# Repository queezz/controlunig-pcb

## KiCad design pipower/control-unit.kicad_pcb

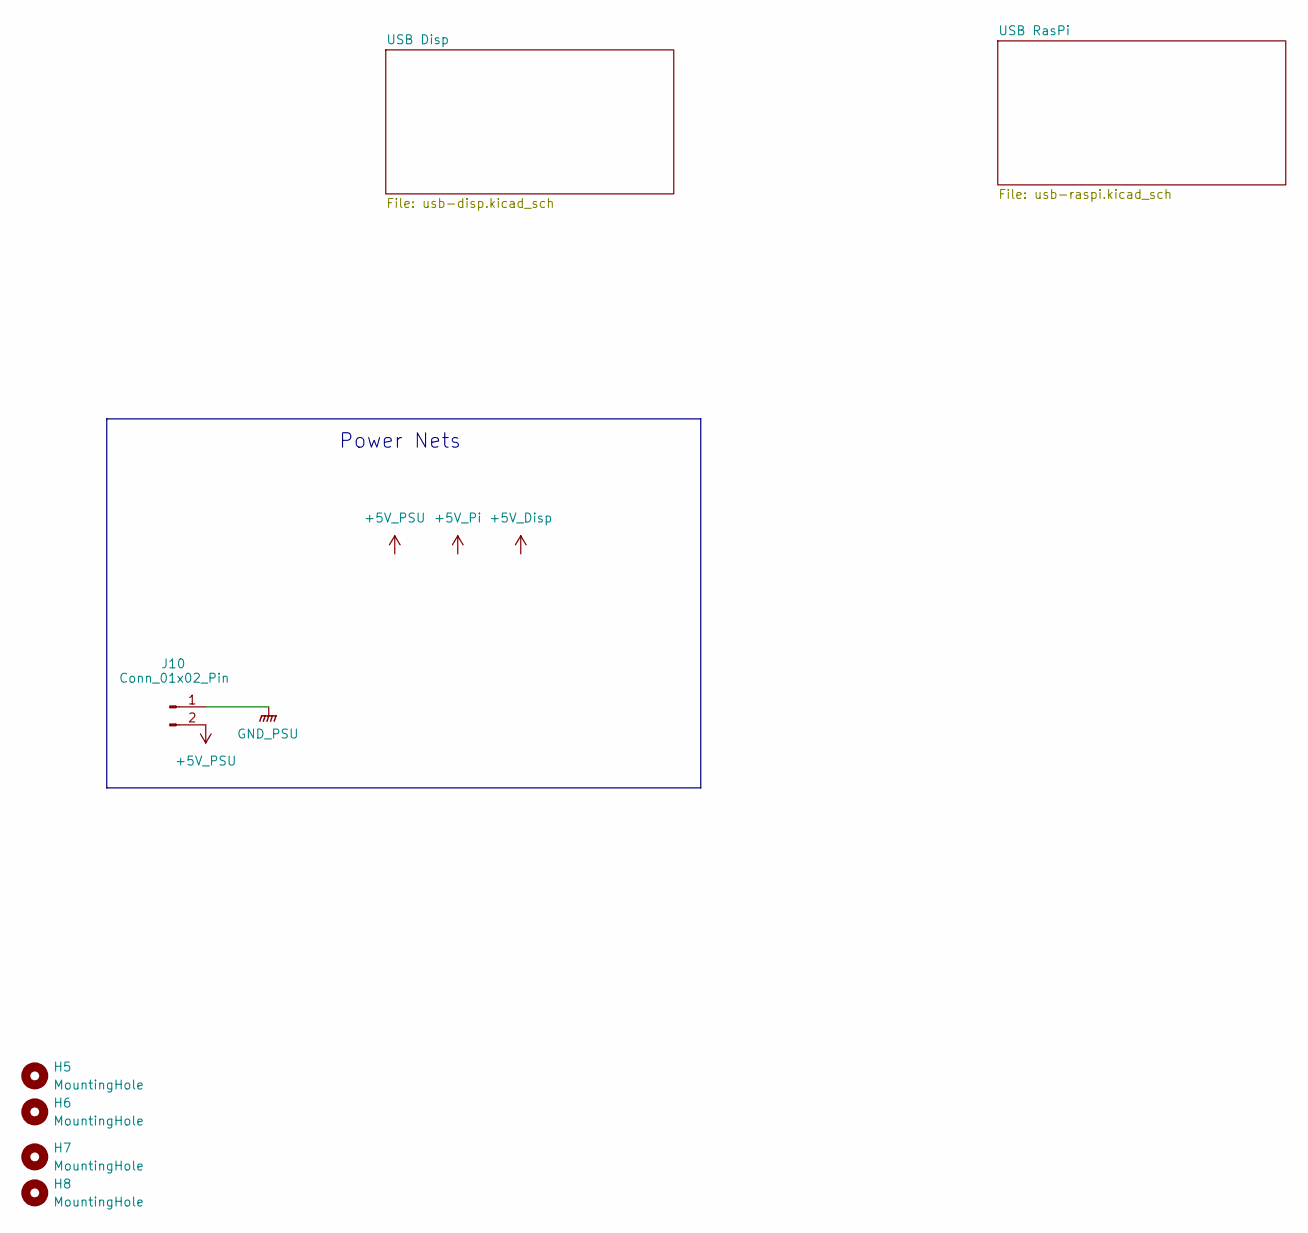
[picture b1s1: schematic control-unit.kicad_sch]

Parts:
H5, H6, H7, H8: MountingHole; MountingHole_3.2mm
J10: Conn_01x02_Pin; JST_VH_B2P-VH-B_1x02_P3.96mm_Vertical

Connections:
+5V_PSU: J10.2; also elsewhere on the board
GND_PSU: J10.1; also elsewhere on the board

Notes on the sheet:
Power Nets

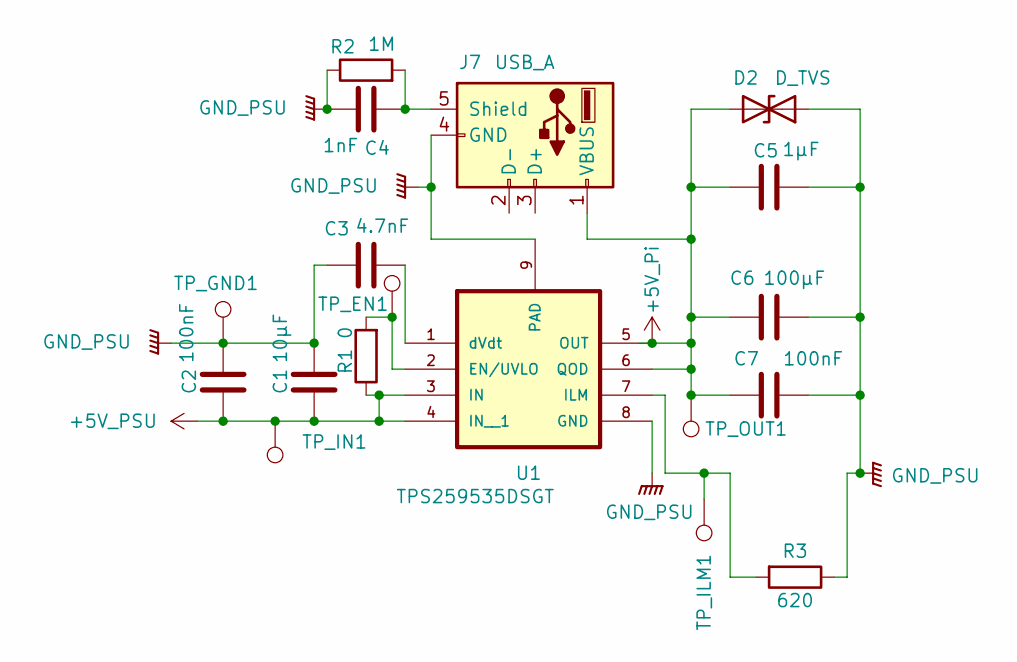
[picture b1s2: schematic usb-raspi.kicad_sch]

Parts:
C1: 10µF; C_0805_2012Metric
C2, C7: 100nF; C_0805_2012Metric
C3: 4.7nF; C_0805_2012Metric
C4: 1nF; C_0805_2012Metric
C5: 1µF; C_0805_2012Metric
C6: 100µF; CP_Elec_6.3x5.8
D2: D_TVS; D_SOD-323_HandSoldering
J7: USB_A; USB_A_Molex_67643_Horizontal
R1: 0; R_0603_1608Metric
R2: 1M; R_0805_2012Metric
R3: 620; R_0805_2012Metric
TP_EN1: TestPoint; TestPoint_Pad_1.0x1.0mm
TP_GND1: TestPoint; TestPoint_Pad_1.0x1.0mm
TP_ILM1: TestPoint; TestPoint_Pad_1.0x1.0mm
TP_IN1: TestPoint; TestPoint_Pad_1.0x1.0mm
TP_OUT1: TestPoint; TestPoint_Pad_1.0x1.0mm
U1: TPS259535DSGT; WSON-8-1EP_2x2mm_P0.5mm_EP0.9x1.6mm

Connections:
+5V_PSU: C1.2, C2.2, R1.1, TP_IN1.1, U1.3 (IN), U1.4 (IN__1); also elsewhere on the board
+5V_Pi: C5.1, C6.1, C7.2, D2.2 (A2), J7.1 (VBUS), TP_OUT1.1, U1.5 (OUT), U1.6 (QOD)
GND_PSU: C1.1, C2.1, C3.1, C4.2, C5.2, C6.2, C7.1, D2.1 (A1), J7.4 (GND), R2.1, R3.1, TP_GND1.1, U1.8 (GND), U1.9 (PAD); also elsewhere on the board
unnamed: C4.1, J7.5 (Shield), R2.2
unnamed: R1.2, TP_EN1.1, U1.2 (EN/UVLO)
unnamed: R3.2, TP_ILM1.1, U1.7 (ILM)
unnamed: C3.2, U1.1 (dVdt)

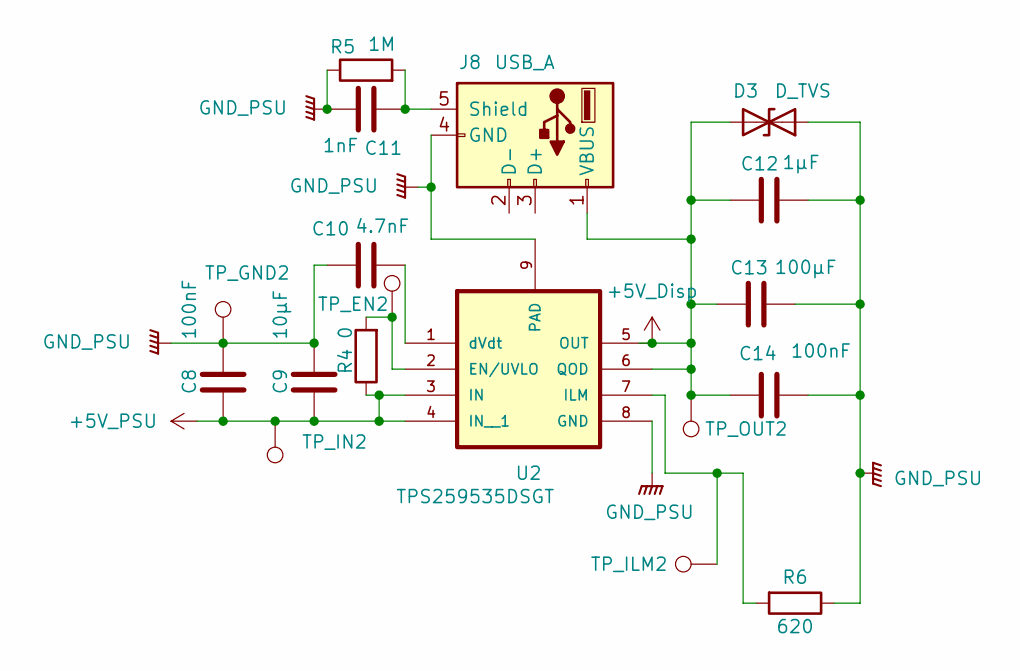
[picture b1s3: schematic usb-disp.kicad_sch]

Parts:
C8, C14: 100nF; C_0805_2012Metric
C9: 10µF; C_0805_2012Metric
C10: 4.7nF; C_0805_2012Metric
C11: 1nF; C_0805_2012Metric
C12: 1µF; C_0805_2012Metric
C13: 100µF; CP_Elec_6.3x5.8
D3: D_TVS; D_SOD-323_HandSoldering
J8: USB_A; USB_A_Molex_67643_Horizontal
R4: 0; R_0603_1608Metric
R5: 1M; R_0805_2012Metric
R6: 620; R_0805_2012Metric
TP_EN2: TestPoint; TestPoint_Pad_1.0x1.0mm
TP_GND2: TestPoint; TestPoint_Pad_1.0x1.0mm
TP_ILM2: TestPoint; TestPoint_Pad_1.0x1.0mm
TP_IN2: TestPoint; TestPoint_Pad_1.0x1.0mm
TP_OUT2: TestPoint; TestPoint_Pad_1.0x1.0mm
U2: TPS259535DSGT; WSON-8-1EP_2x2mm_P0.5mm_EP0.9x1.6mm

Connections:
+5V_Disp: C12.1, C13.1, C14.2, D3.2 (A2), J8.1 (VBUS), TP_OUT2.1, U2.5 (OUT), U2.6 (QOD)
+5V_PSU: C8.2, C9.2, R4.1, TP_IN2.1, U2.3 (IN), U2.4 (IN__1); also elsewhere on the board
GND_PSU: C8.1, C9.1, C10.1, C11.2, C12.2, C13.2, C14.1, D3.1 (A1), J8.4 (GND), R5.1, R6.1, TP_GND2.1, U2.8 (GND), U2.9 (PAD); also elsewhere on the board
unnamed: C11.1, J8.5 (Shield), R5.2
unnamed: R4.2, TP_EN2.1, U2.2 (EN/UVLO)
unnamed: R6.2, TP_ILM2.1, U2.7 (ILM)
unnamed: C10.2, U2.1 (dVdt)

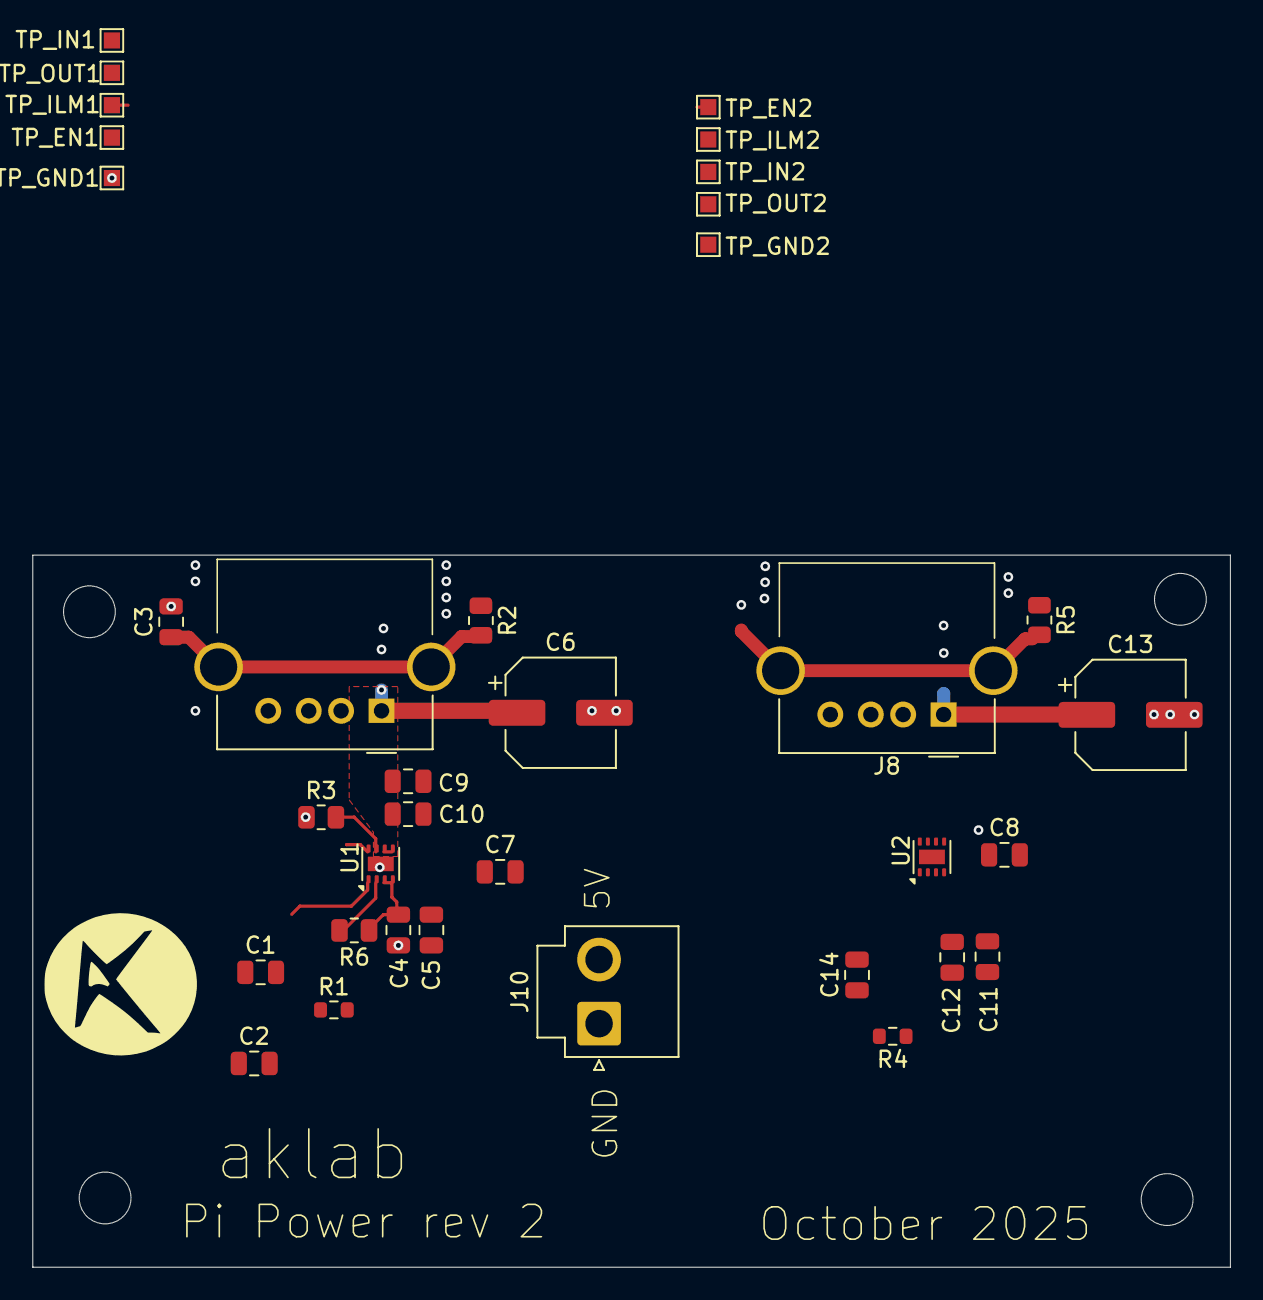
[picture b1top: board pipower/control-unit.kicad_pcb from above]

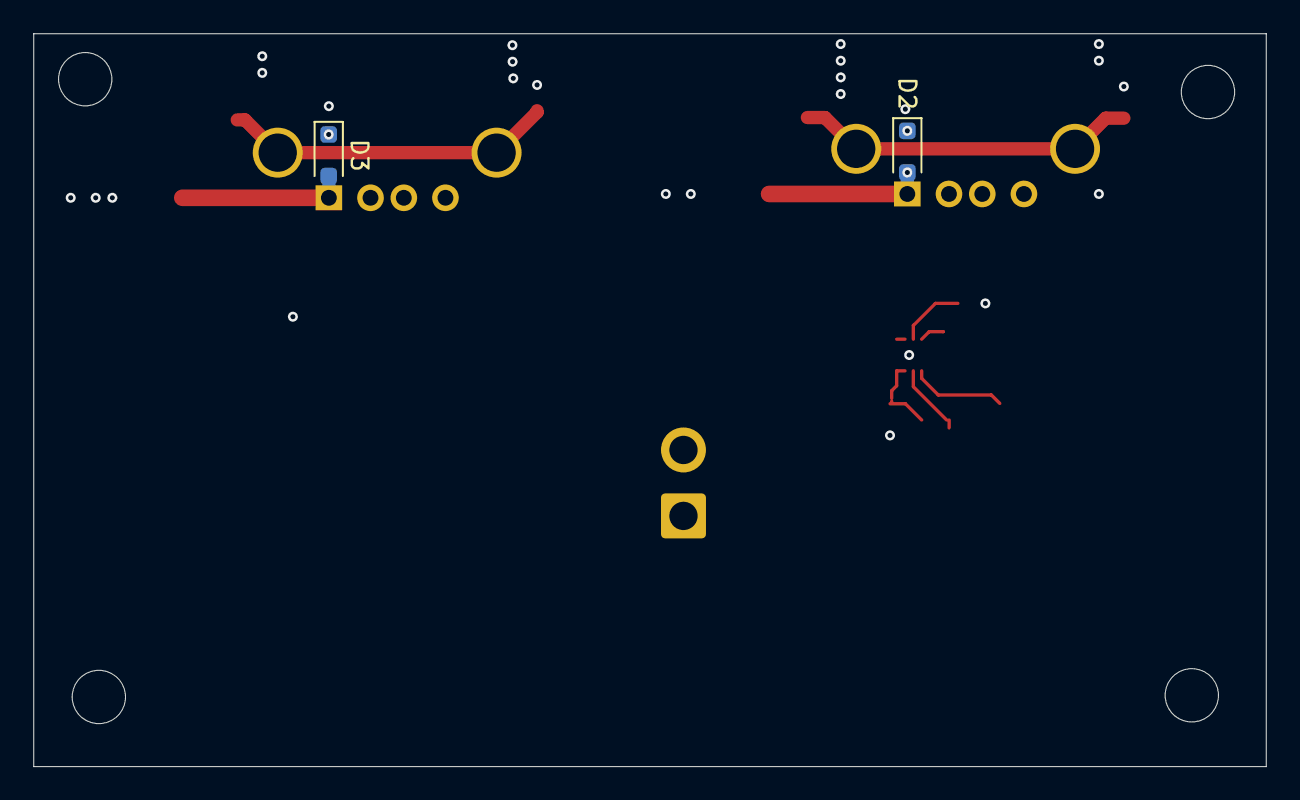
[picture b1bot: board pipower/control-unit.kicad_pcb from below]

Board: 2 copper layers, 74.0 x 44.0 mm, 41 parts (2 on the bottom side), 12 nets.

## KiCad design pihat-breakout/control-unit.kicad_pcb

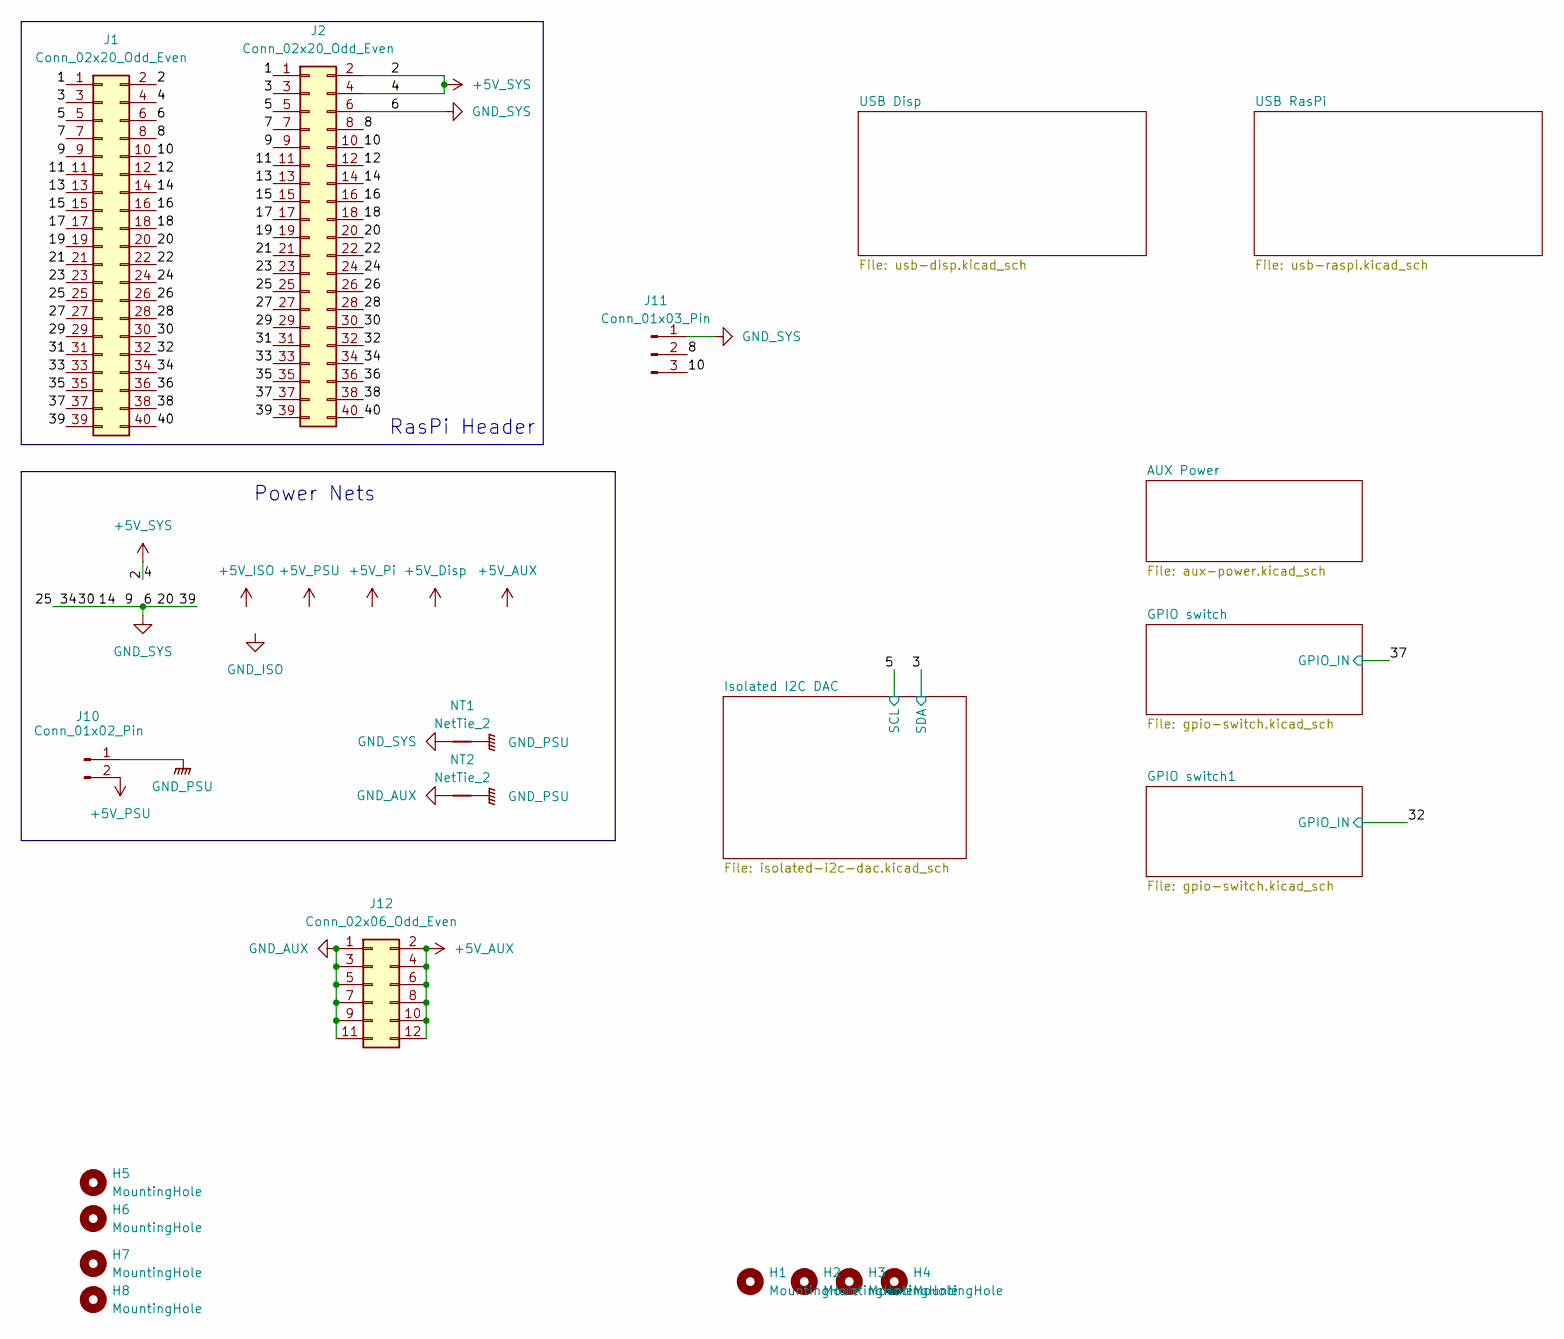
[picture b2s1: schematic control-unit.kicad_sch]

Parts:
H1, H2, H3, H4: MountingHole; MountingHole_2.7mm
H5, H6, H7, H8: MountingHole; MountingHole_3.2mm
J1, J2: Conn_02x20_Odd_Even; RasPiHeader_2x20_P2.54mm_Vertical
J10: Conn_01x02_Pin; JST_VH_B2P-VH-B_1x02_P3.96mm_Vertical
J11: Conn_01x03_Pin; JST_XH_B3B-XH-A_1x03_P2.50mm_Vertical
J12: Conn_02x06_Odd_Even; PinHeader_2x06_P2.54mm_Vertical
NT1, NT2: NetTie_2; NetTie-2_SMD_Pad2.0mm

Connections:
+5V_AUX: J12.2, J12.4, J12.6, J12.8, J12.10, J12.12; also elsewhere on the board
+5V_PSU: J10.2; also elsewhere on the board
+5V_SYS: J1.2, J1.4, J2.2, J2.4; also elsewhere on the board
/1: J1.1, J2.1
/3: J1.3, J2.3; also elsewhere on the board
/5: J1.5, J2.5; also elsewhere on the board
/7: J1.7, J2.7
/8: J1.8, J2.8, J11.2
/10: J1.10, J2.10, J11.3
/11: J1.11, J2.11
/12: J1.12, J2.12
/13: J1.13, J2.13
/15: J1.15, J2.15
/16: J1.16, J2.16
/17: J1.17, J2.17
/18: J1.18, J2.18
/19: J1.19, J2.19
/21: J1.21, J2.21
/22: J1.22, J2.22
/23: J1.23, J2.23
/24: J1.24, J2.24
/26: J1.26, J2.26
/27: J1.27, J2.27
/28: J1.28, J2.28
/29: J1.29, J2.29
/31: J1.31, J2.31
/32: J1.32, J2.32; also elsewhere on the board
/33: J1.33, J2.33
/35: J1.35, J2.35
/36: J1.36, J2.36
/37: J1.37, J2.37; also elsewhere on the board
/38: J1.38, J2.38
/40: J1.40, J2.40
GND_AUX: J12.1, J12.3, J12.5, J12.7, J12.9, J12.11, NT2.1; also elsewhere on the board
GND_PSU: J10.1, NT1.2, NT2.2; also elsewhere on the board
GND_SYS: J1.6, J1.9, J1.14, J1.20, J1.25, J1.30, J1.34, J1.39, J2.6, J2.9, J2.14, J2.20, J2.25, J2.30, J2.34, J2.39, J11.1, NT1.1; also elsewhere on the board

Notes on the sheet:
RasPi Header
Power Nets

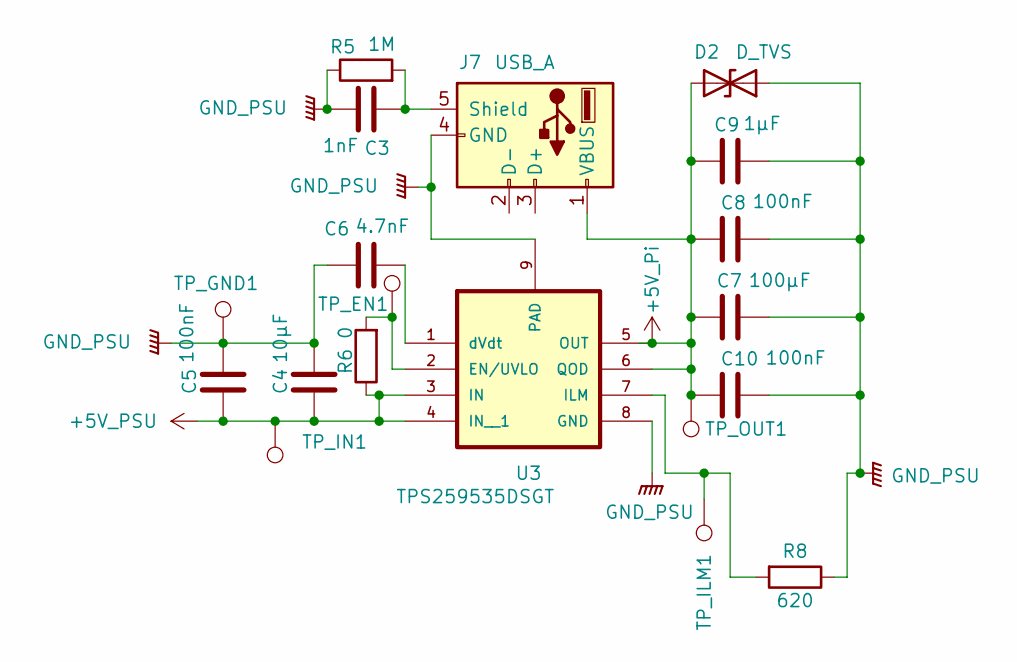
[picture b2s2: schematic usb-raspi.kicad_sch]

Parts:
C3: 1nF; C_0603_1608Metric
C4: 10µF; C_0603_1608Metric
C5, C8, C10: 100nF; C_0603_1608Metric
C6: 4.7nF; C_0603_1608Metric
C7: 100µF; CP_Elec_6.3x5.8
C9: 1µF; C_0603_1608Metric
D2: D_TVS; D_SOD-323_HandSoldering
J7: USB_A; USB_A_Molex_67643_Horizontal
R5: 1M; R_0603_1608Metric
R6: 0; R_0603_1608Metric
R8: 620; R_0603_1608Metric
TP_EN1: TestPoint; TestPoint_Pad_1.0x1.0mm
TP_GND1: TestPoint; TestPoint_Pad_1.0x1.0mm
TP_ILM1: TestPoint; TestPoint_Pad_1.0x1.0mm
TP_IN1: TestPoint; TestPoint_Pad_1.0x1.0mm
TP_OUT1: TestPoint; TestPoint_Pad_1.0x1.0mm
U3: TPS259535DSGT; WSON-8-1EP_3x3mm_P0.5mm_EP1.6x2.0mm

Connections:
+5V_PSU: C4.2, C5.2, R6.1, TP_IN1.1, U3.3 (IN), U3.4 (IN__1); also elsewhere on the board
+5V_Pi: C7.1, C8.2, C9.1, C10.2, D2.2 (A2), J7.1 (VBUS), TP_OUT1.1, U3.5 (OUT), U3.6 (QOD)
GND_PSU: C3.2, C4.1, C5.1, C6.1, C7.2, C8.1, C9.2, C10.1, D2.1 (A1), J7.4 (GND), R5.1, R8.1, TP_GND1.1, U3.8 (GND), U3.9 (PAD); also elsewhere on the board
unnamed: C3.1, J7.5 (Shield), R5.2
unnamed: R6.2, TP_EN1.1, U3.2 (EN/UVLO)
unnamed: R8.2, TP_ILM1.1, U3.7 (ILM)
unnamed: C6.2, U3.1 (dVdt)

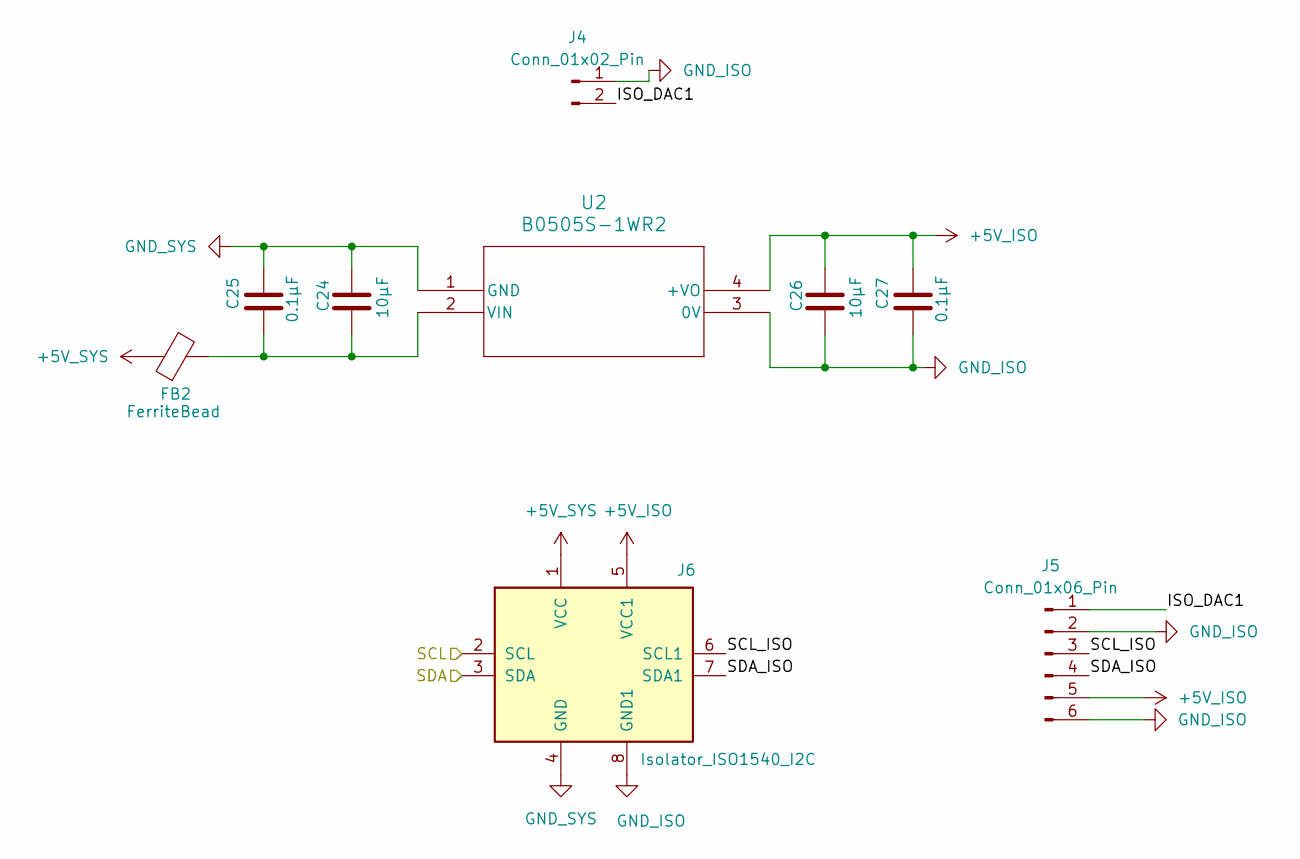
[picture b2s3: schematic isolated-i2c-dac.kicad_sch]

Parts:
C24: 10µF; C_0805_2012Metric
C25, C27: 0.1µF; C_0603_1608Metric
C26: 10µF; C_1206_3216Metric
FB2: FerriteBead; R_0805_2012Metric
J4: Conn_01x02_Pin; JST_XH_B2B-XH-A_1x02_P2.50mm_Vertical
J5: Conn_01x06_Pin; MCP4725_module
J6: Isolator_ISO1540_I2C; Isolator_ISO_1540_module
U2: B0505S-1WR2; B0505S-1WR2_MNS

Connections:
+5V_ISO: C26.1, C27.1, J5.5, J6.5 (VCC1), U2.4 (+VO)
+5V_SYS: FB2.1, J6.1 (VCC); also elsewhere on the board
/3: J6.3 (SDA); also elsewhere on the board
/5: J6.2 (SCL); also elsewhere on the board
/Isolated I2C DAC/ISO_DAC1: J4.2, J5.1
/Isolated I2C DAC/SCL_ISO: J5.3, J6.6 (SCL1)
/Isolated I2C DAC/SDA_ISO: J5.4, J6.7 (SDA1)
GND_ISO: C26.2, C27.2, J4.1, J5.2, J5.6, J6.8 (GND1), U2.3 (0V)
GND_SYS: C24.1, C25.1, J6.4 (GND), U2.1 (GND); also elsewhere on the board
unnamed: C24.2, C25.2, FB2.2, U2.2 (VIN)

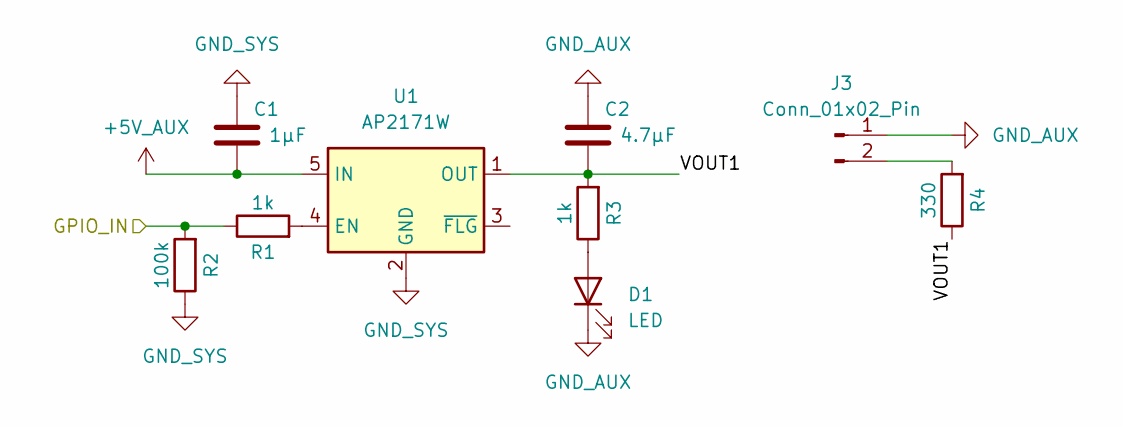
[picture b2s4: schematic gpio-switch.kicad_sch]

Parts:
C1: 1µF; C_0603_1608Metric
C2: 4.7µF; C_0603_1608Metric
D1: LED; LED_0603_1608Metric
J3: Conn_01x02_Pin; JST_XH_B2B-XH-A_1x02_P2.50mm_Vertical
R1, R3: 1k; R_0603_1608Metric
R2: 100k; R_0603_1608Metric
R4: 330; R_0603_1608Metric
U1: AP2171W; SOT-23-5

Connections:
+5V_AUX: C1.2, U1.5 (IN); also elsewhere on the board
/37: R1.1, R2.2; also elsewhere on the board
/GPIO switch/VOUT1: C2.2, R3.2, R4.1, U1.1 (OUT)
GND_AUX: C2.1, D1.1 (K), J3.1; also elsewhere on the board
GND_SYS: C1.1, R2.1, U1.2 (GND); also elsewhere on the board
unnamed: D1.2 (A), R3.1
unnamed: J3.2, R4.2
unnamed: R1.2, U1.4 (EN)

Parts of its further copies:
C22: 1µF; C_0603_1608Metric
C23: 4.7µF; C_0603_1608Metric
D6: LED; LED_0603_1608Metric
J9: Conn_01x02_Pin; JST_XH_B2B-XH-A_1x02_P2.50mm_Vertical
R12: 100k; R_0603_1608Metric
R14, R15: 1k; R_0603_1608Metric
R16: 330; R_0603_1608Metric
U6: AP2171W; SOT-23-5

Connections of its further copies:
+5V_AUX: C22.2, U6.5 (IN); also elsewhere on the board
/32: R12.2, R14.1; also elsewhere on the board
/GPIO switch1/VOUT1: C23.2, R15.2, R16.1, U6.1 (OUT)
GND_AUX: C23.1, D6.1 (K), J9.1; also elsewhere on the board
GND_SYS: C22.1, R12.1, U6.2 (GND); also elsewhere on the board
unnamed: D6.2 (A), R15.1
unnamed: J9.2, R16.2
unnamed: R14.2, U6.4 (EN)

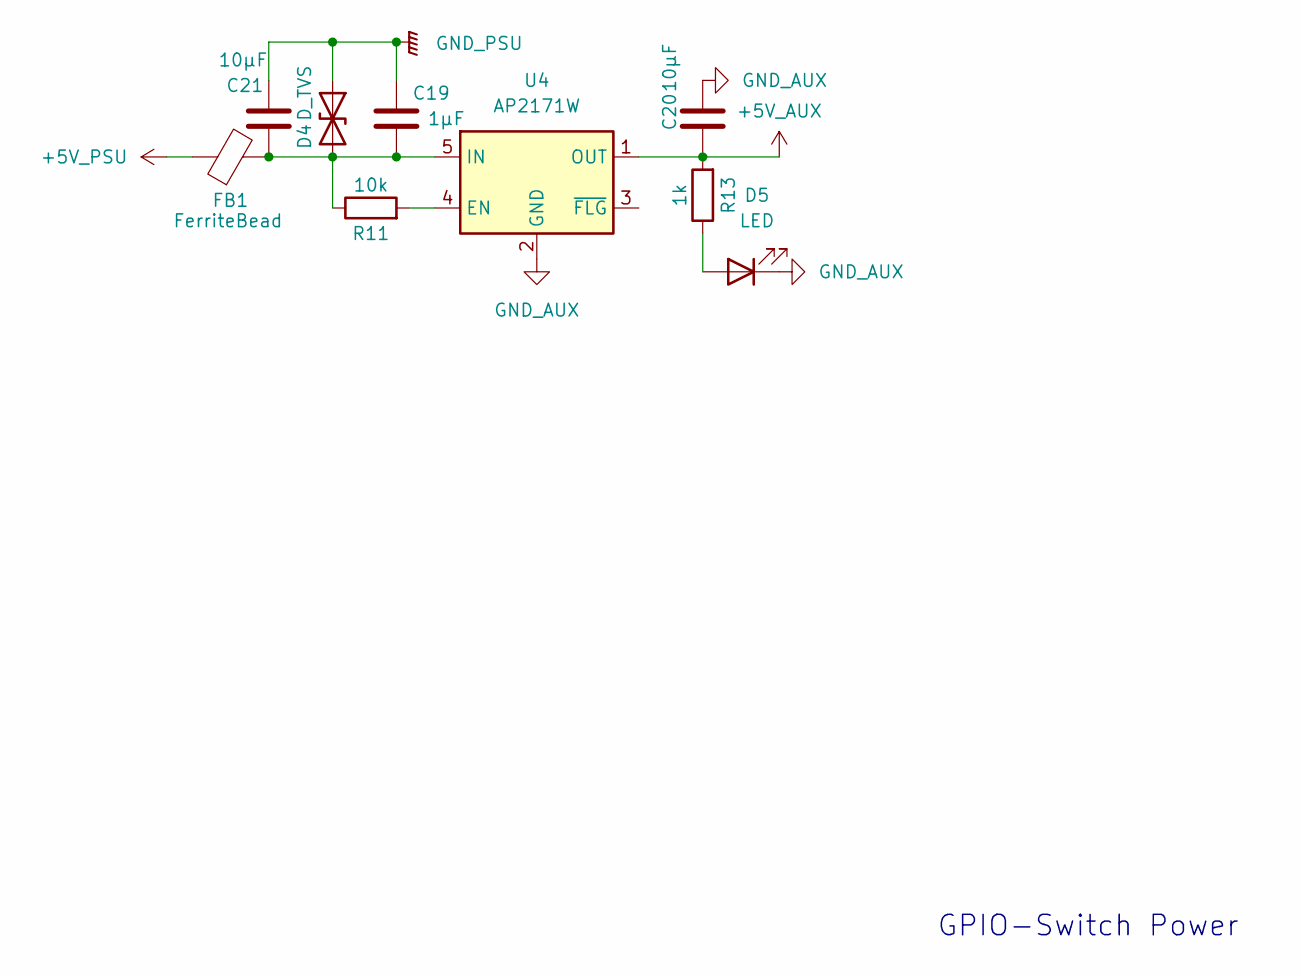
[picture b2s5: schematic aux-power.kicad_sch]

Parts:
C19: 1µF; C_0603_1608Metric
C20, C21: 10µF; C_0603_1608Metric
D4: D_TVS; D_SOD-323_HandSoldering
D5: LED; LED_0603_1608Metric
FB1: FerriteBead; R_0603_1608Metric
R11: 10k; R_0603_1608Metric
R13: 1k; R_0603_1608Metric
U4: AP2171W; SOT-23-5

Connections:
+5V_AUX: C20.2, R13.2, U4.1 (OUT); also elsewhere on the board
+5V_PSU: FB1.1; also elsewhere on the board
GND_AUX: C20.1, D5.1 (K), U4.2 (GND); also elsewhere on the board
GND_PSU: C19.1, C21.1, D4.1 (A1); also elsewhere on the board
unnamed: C19.2, C21.2, D4.2 (A2), FB1.2, R11.1, U4.5 (IN)
unnamed: D5.2 (A), R13.1
unnamed: R11.2, U4.4 (EN)

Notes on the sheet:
GPIO-Switch Power

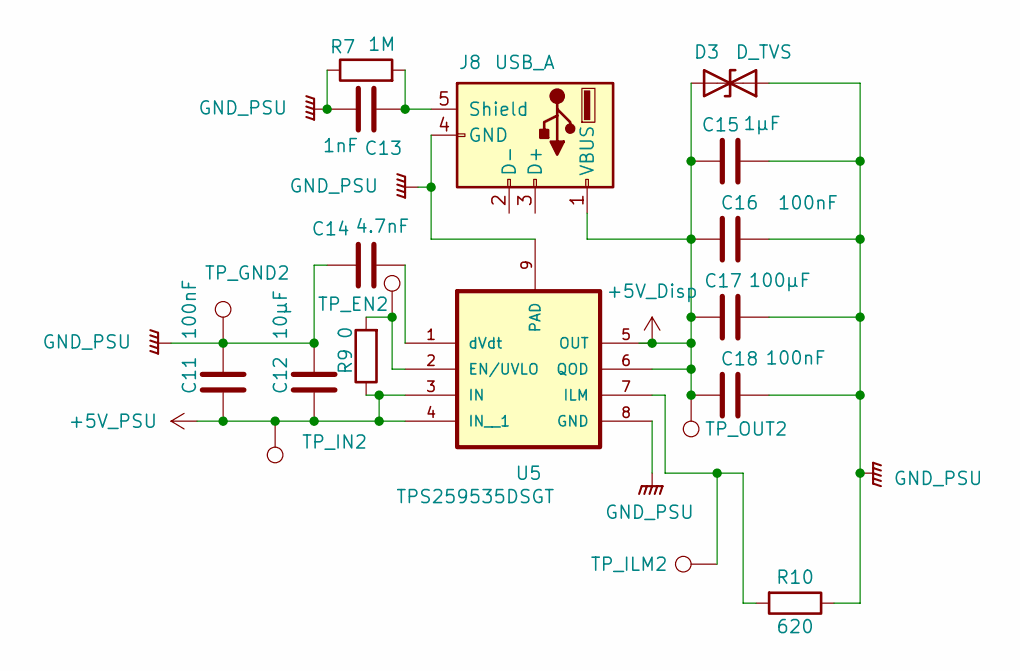
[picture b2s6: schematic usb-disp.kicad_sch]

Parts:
C11, C16, C18: 100nF; C_0603_1608Metric
C12: 10µF; C_0603_1608Metric
C13: 1nF; C_0603_1608Metric
C14: 4.7nF; C_0603_1608Metric
C15: 1µF; C_0603_1608Metric
C17: 100µF; CP_Elec_6.3x5.8
D3: D_TVS; D_SOD-323_HandSoldering
J8: USB_A; USB_A_Molex_67643_Horizontal
R7: 1M; R_0603_1608Metric
R9: 0; R_0603_1608Metric
R10: 620; R_0603_1608Metric
TP_EN2: TestPoint; TestPoint_Pad_1.0x1.0mm
TP_GND2: TestPoint; TestPoint_Pad_1.0x1.0mm
TP_ILM2: TestPoint; TestPoint_Pad_1.0x1.0mm
TP_IN2: TestPoint; TestPoint_Pad_1.0x1.0mm
TP_OUT2: TestPoint; TestPoint_Pad_1.0x1.0mm
U5: TPS259535DSGT; WSON-8-1EP_3x3mm_P0.5mm_EP1.6x2.0mm

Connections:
+5V_Disp: C15.1, C16.2, C17.1, C18.2, D3.2 (A2), J8.1 (VBUS), TP_OUT2.1, U5.5 (OUT), U5.6 (QOD)
+5V_PSU: C11.2, C12.2, R9.1, TP_IN2.1, U5.3 (IN), U5.4 (IN__1); also elsewhere on the board
GND_PSU: C11.1, C12.1, C13.2, C14.1, C15.2, C16.1, C17.2, C18.1, D3.1 (A1), J8.4 (GND), R7.1, R10.1, TP_GND2.1, U5.8 (GND), U5.9 (PAD); also elsewhere on the board
unnamed: C13.1, J8.5 (Shield), R7.2
unnamed: R9.2, TP_EN2.1, U5.2 (EN/UVLO)
unnamed: R10.2, TP_ILM2.1, U5.7 (ILM)
unnamed: C14.2, U5.1 (dVdt)

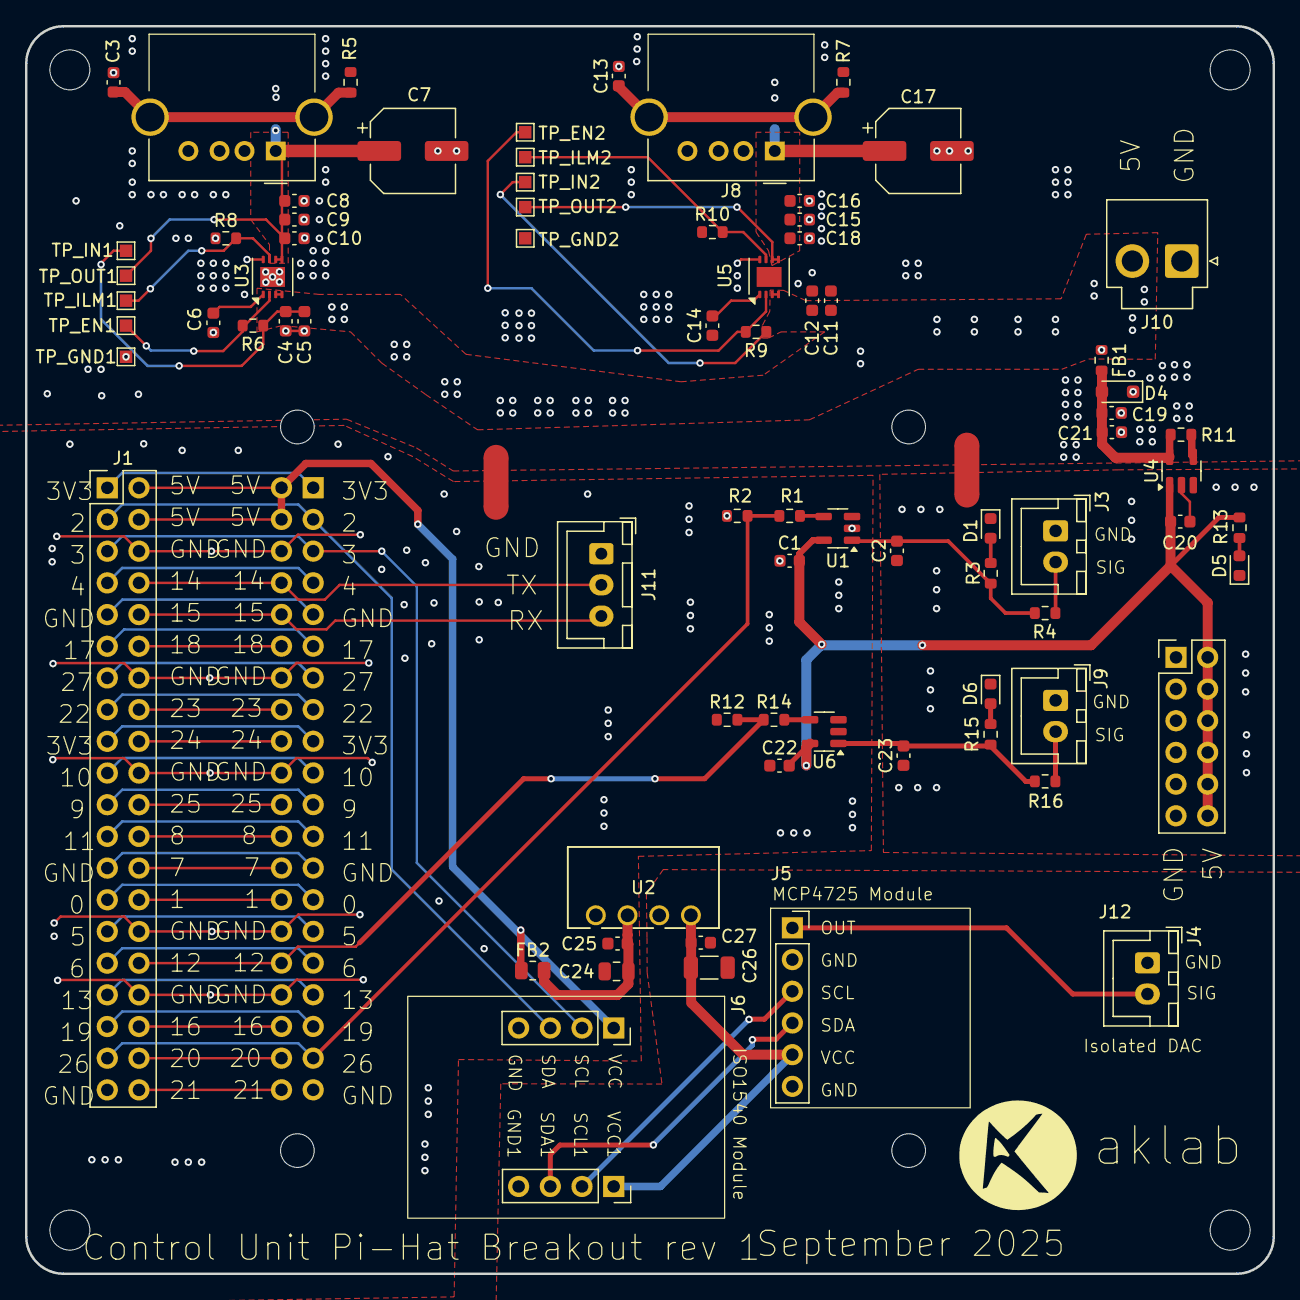
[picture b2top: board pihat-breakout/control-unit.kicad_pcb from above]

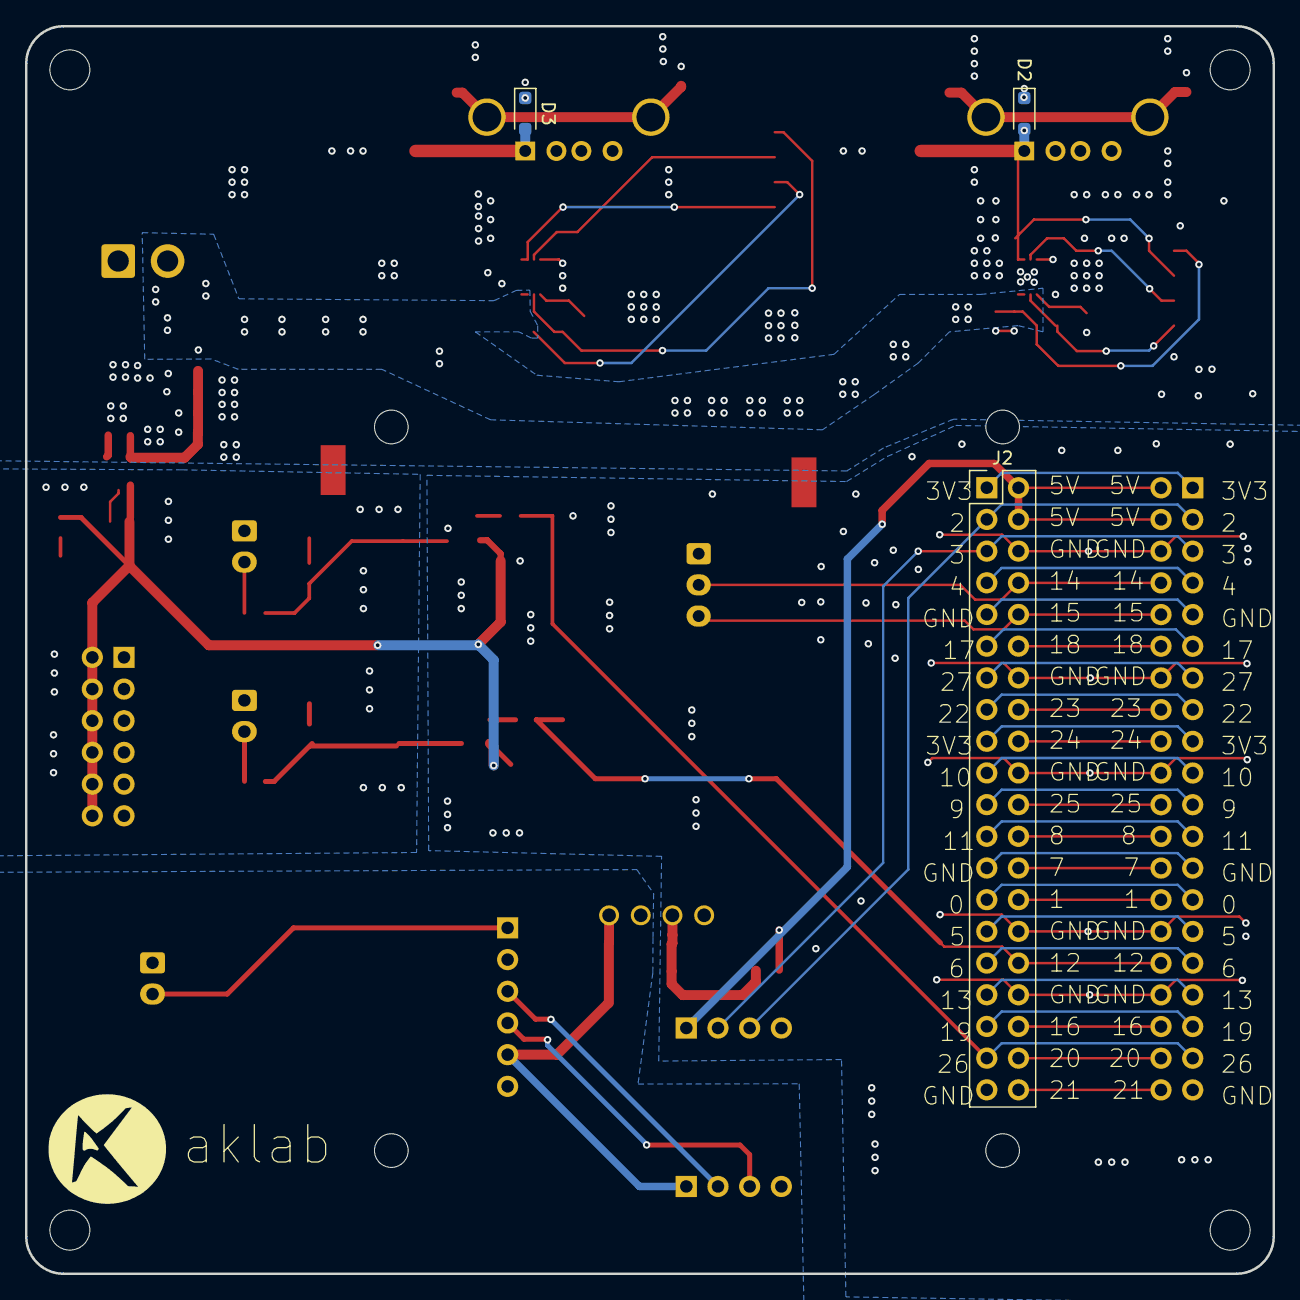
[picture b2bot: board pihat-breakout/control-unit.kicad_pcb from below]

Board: 2 copper layers, 100.0 x 100.0 mm, 89 parts (3 on the bottom side), 63 nets.
